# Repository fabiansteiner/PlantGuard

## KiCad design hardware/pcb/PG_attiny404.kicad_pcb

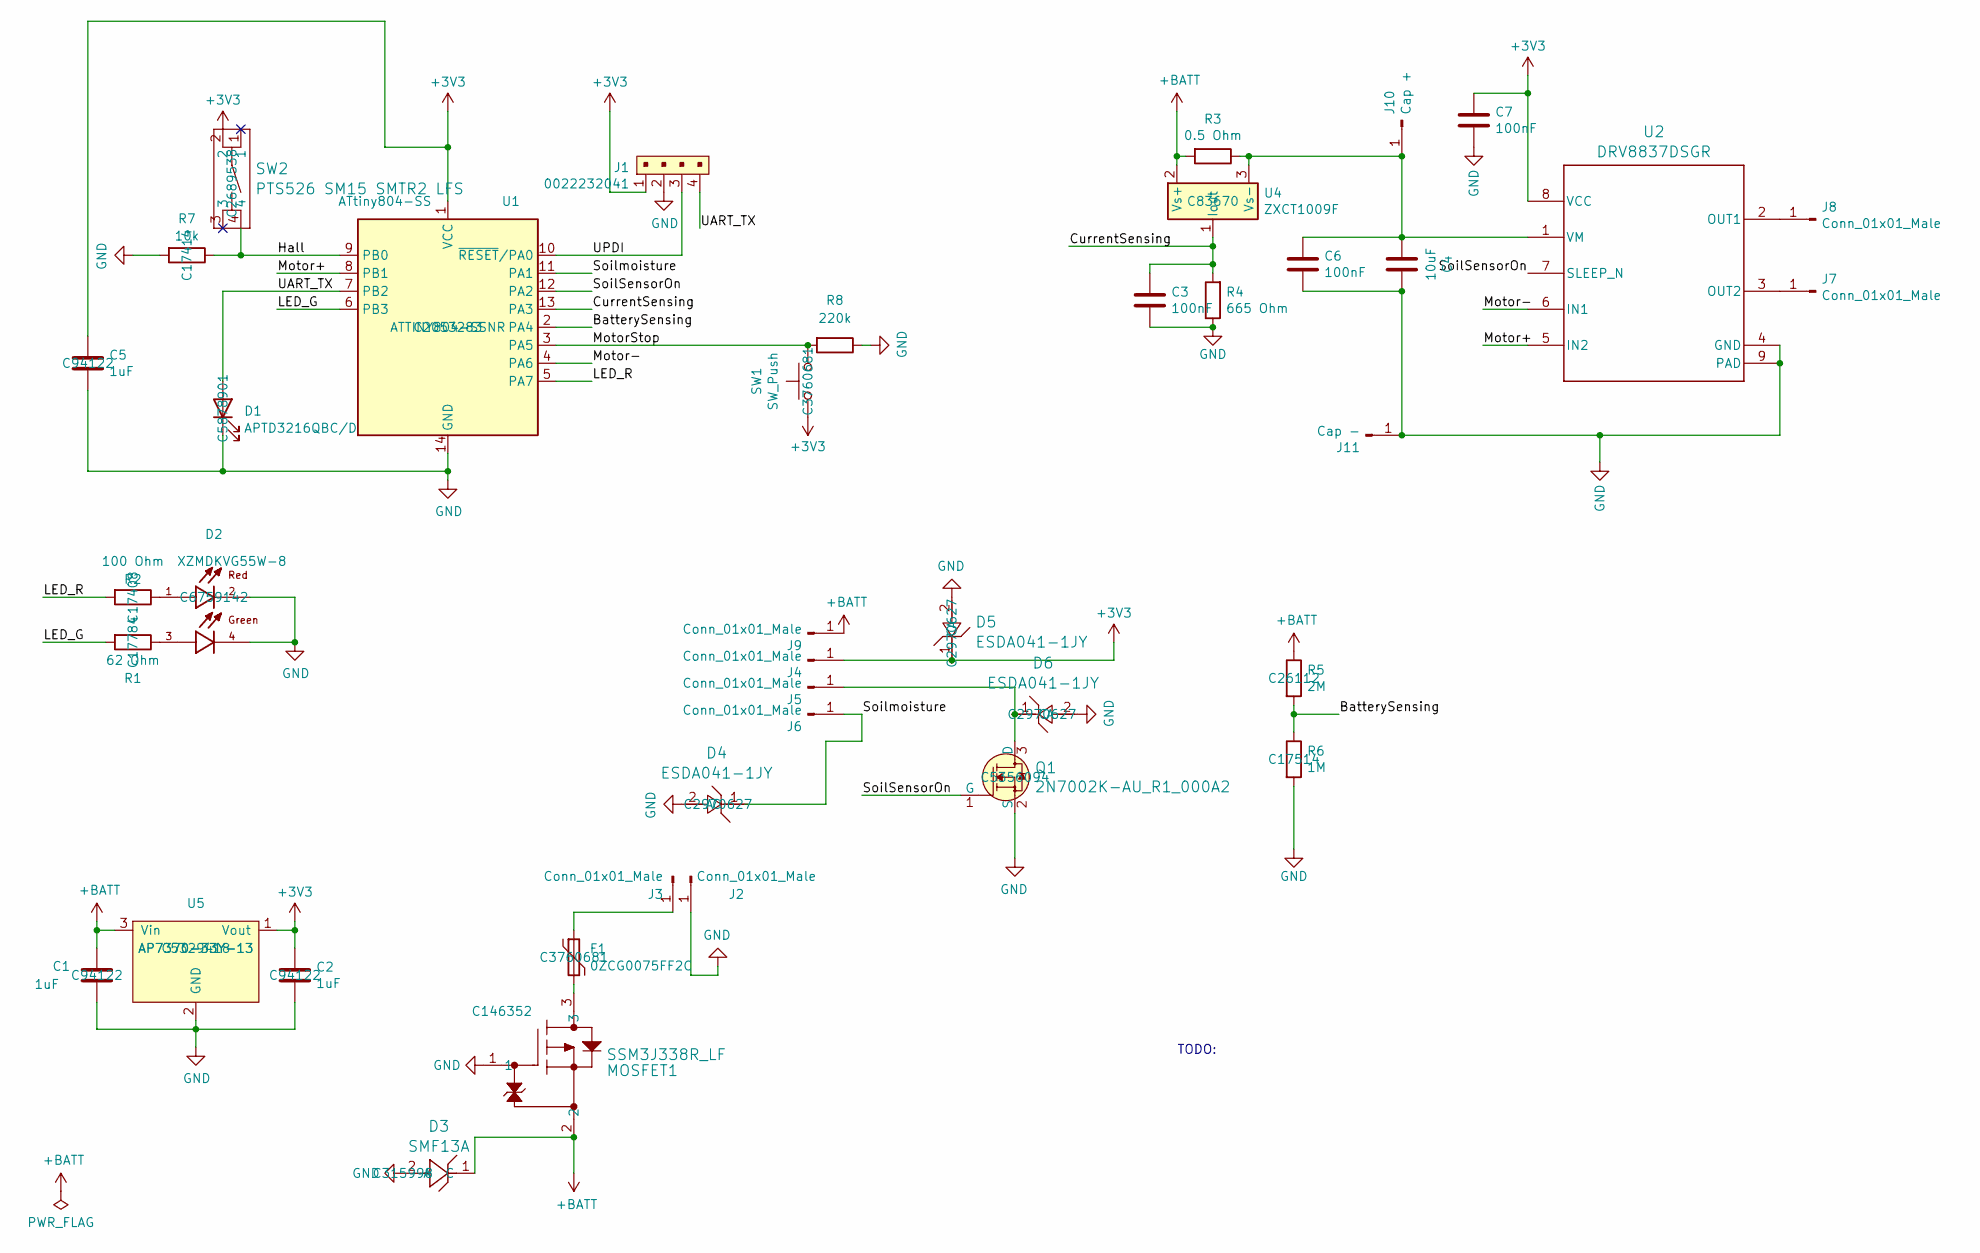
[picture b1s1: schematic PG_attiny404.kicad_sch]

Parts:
C1, C2, C5: 1uF; C_0805_2012Metric_Pad1.18x1.45mm_HandSolder; MPN CL21B105KOFNNNE; JLC C94122
C3, C6, C7: 100nF; C_0805_2012Metric_Pad1.18x1.45mm_HandSolder; MPN CC0805KRX7R7BB104; JLC C519980
C4: 10uF; C_0805_2012Metric_Pad1.18x1.45mm_HandSolder; MPN CL21A106KOQNNNG; JLC C326595
D1: APTD3216QBC/D; LED_1206_3216Metric_Pad1.42x1.75mm_HandSolder; MPN APTD3216QBC/D; JLC C5878901
D2: XZMDKVG55W-8; LED_XZMDKVG55W-8; MPN XZMDKVG55W-8; DigiKey_Part_Number 1497-1183-2-ND
D3: SMF13A; SMFSeries_LTF; MPN SMF13A; JLC C315998
D4, D5, D6: ESDA041-1JY; CR_041-1JY_STM; MPN ESDA041-1JY; JLC C2970627
F1: 0ZCG0075FF2C; MPN 0ZCG0075FF2C; JLC C3760681
J1: 0022232041; PinHeader_1x4_P2.54mm_Drill1.02mm; MPN 0022286040; Digi-Key_PN WM4202-ND
J2, J3, J4, J5, J6, J7, J8, J9: Conn_01x01_Male; PROBE_PAD_1206
J10: Cap +; PROBE_PAD_0603
J11: Cap -; PROBE_PAD_0603
MOSFET1: SSM3J338R_LF; SOT-23F_TOS; MPN SSM3J338R,LF; JLC C146352
Q1: 2N7002K-AU_R1_000A2; SOT-23_Handsoldering; MPN 2N7002K-AU_R1_000A2; Digi-Key_PN 2N7002NCT-ND
R1: 62 Ohm; R_0805_2012Metric_Pad1.20x1.40mm_HandSolder; MPN RMCF0805FT62R0; JLC C17784
R2: 100 Ohm; R_0805_2012Metric_Pad1.20x1.40mm_HandSolder; MPN RMCF0805FT100R; JLC C17408
R3: 0.5 Ohm; R_0805_2012Metric_Pad1.20x1.40mm_HandSolder; MPN RL1220S-R50-F; JLC C859814
R4: 665 Ohm; R_0805_2012Metric_Pad1.20x1.40mm_HandSolder; MPN CRGCQ0805F680R; JLC C17798
R5: 2M; R_0805_2012Metric_Pad1.20x1.40mm_HandSolder; MPN RMCF0805FT2M00; JLC C26112
R6: 1M; R_0805_2012Metric_Pad1.20x1.40mm_HandSolder; MPN RMCF0805FG1M00; JLC C17514
R7: 10k; R_0805_2012Metric_Pad1.20x1.40mm_HandSolder; MPN ERJ-6GEYJ103V; JLC C17414
R8: 220k; R_0805_2012Metric_Pad1.20x1.40mm_HandSolder; MPN CRG0805F220K; JLC C17556
SW1: SW_Push; 1825027-2; MPN 1825027-2; JLC C3760681
SW2: PTS526 SM15 SMTR2 LFS; PTS526SK15SMTR2 LFS-M; MPN PTS526SM15SMTR2 LFS; JLC C2689538
U1: ATtiny804-SS; SOIC-14_3.9x8.7mm_P1.27mm; MPN ATTINY804-SSNR; JLC C2053283
U2: DRV8837DSGR; DRV8837DSGR_NV; MPN DRV8837DSGR; JLC C39159
U4: ZXCT1009F; SOT-23_Handsoldering_ZXCT1009F; MPN ZXCT1009FTA; JLC C83670
U5: AP7370-33Y-13; SOT-89-3; MPN AP7370-33Y-13; JLC C5329418

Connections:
+3V3: C2.2, C5.2, C7.2, D5.1 (C), J1.1, J4.1, SW1.2, SW2.2, U1.1 (VCC), U2.8 (VCC), U5.1 (Vout)
+BATT: C1.2, D3.1 (C), J9.1, MOSFET1.2, R3.2, R5.1, U4.2 (Vs+), U5.3 (Vin)
/BatterySensing: R5.2, R6.1, U1.2 (PA4)
/CurrentSensing: C3.2, R4.2, U1.13 (PA3), U4.1 (Iout)
/Hall: R7.1, SW2.4, U1.9 (PB0)
/LED_G: R1.2, U1.6 (PB3)
/LED_R: R2.2, U1.5 (PA7)
/Motor+: U1.8 (PB1), U2.5 (IN2)
/Motor-: U1.4 (PA6), U2.6 (IN1)
/MotorStop: R8.2, SW1.1, U1.3 (PA5)
/SoilSensorOn: Q1.1 (G), U1.12 (PA2), U2.7 (SLEEP_N)
/Soilmoisture: D4.1 (C), J6.1, U1.11 (PA1)
/UART_TX: D1.2 (A), J1.4, U1.7 (PB2)
/UPDI: J1.3, U1.10 (~RESET/PA0)
GND: C1.1, C2.1, C3.1, C4.1, C5.1, C6.1, C7.1, D1.1 (K), D2.2, D2.4, D3.2 (A), D4.2 (A), D5.2 (A), D6.2 (A), J1.2, J2.1, J11.1, MOSFET1.1, Q1.2 (S), R4.1, R6.2, R7.2, R8.1, U1.14 (GND), U2.4 (GND), U2.9 (PAD), U5.2 (GND)
unnamed: D2.1, R2.1
unnamed: D2.3, R1.1
unnamed: D6.1 (C), J5.1, Q1.3 (D)
unnamed: F1.2, MOSFET1.3
unnamed: F1.1, J3.1
unnamed: J7.1, U2.3 (OUT2)
unnamed: J8.1, U2.2 (OUT1)
unnamed: C4.2, C6.2, J10.1, R3.1, U2.1 (VM), U4.3 (Vs-)

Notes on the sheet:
TODO:

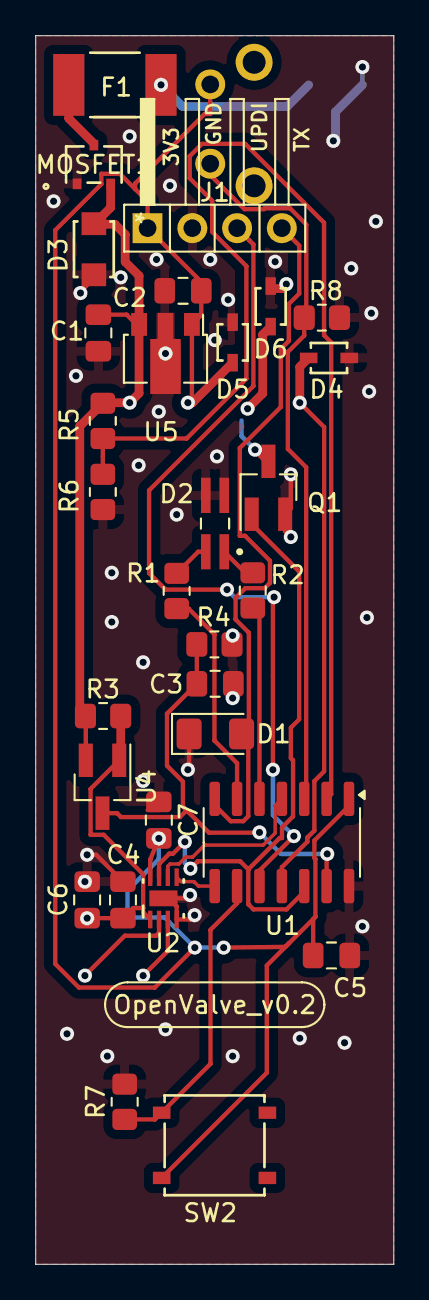
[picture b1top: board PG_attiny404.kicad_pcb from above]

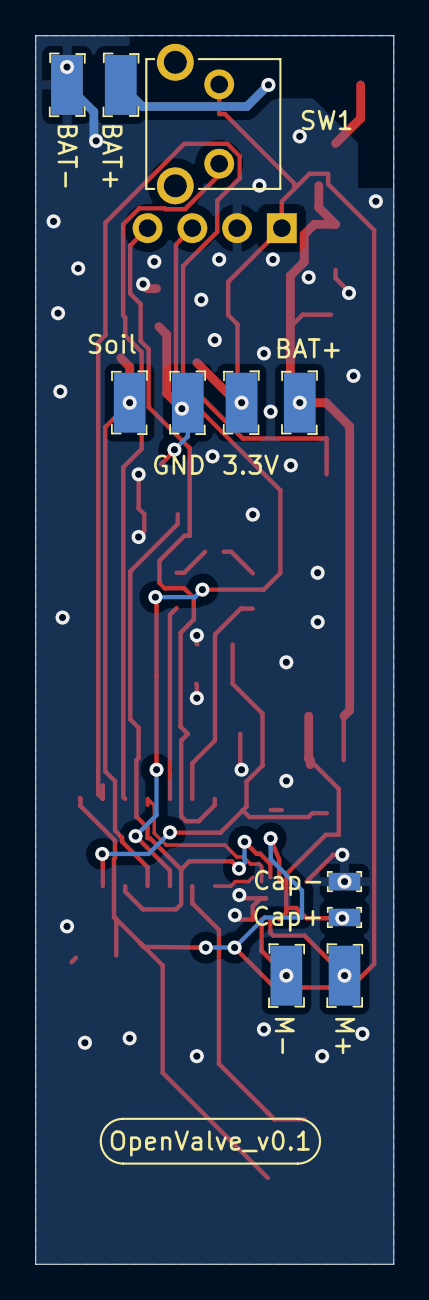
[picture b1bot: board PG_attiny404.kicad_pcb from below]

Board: 2 copper layers, 20.3 x 69.7 mm, 41 parts (11 on the bottom side), 23 nets.

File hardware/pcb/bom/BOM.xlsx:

Reference | Value | DK_Detail_Page | Menge
C1, C2, C5 | 1uF | https://www.digikey.at/de/products/detail/samsung-electro-me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 | 3
C3, C6 | 100nF | https://www.digikey.at/de/products/detail/yageo/CC0805KRX7R7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 | 2
C4 | 10uF | https://www.digikey.at/de/products/detail/samsung-electro-me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 | 1
D1 | APTD3216QBC/D | https://www.digikey.at/de/products/detail/kingbright/APTD321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 | 1
D2 | XZMDKVG55W-8 | https://www.digikey.at/de/products/detail/sunled/XZMDKVG55W-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 | 1
J1 | 0022232041 | https://www.digikey.at/de/products/detail/molex/0022286040/3158671 | 1
J2-J9 | Conn_01x01_Male |  | 8
Q1 | 2N7002 | https://www.digikey.at/de/products/detail/panjit-internation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 | 1
R1, R2 | 68 Ohm | https://www.digikey.at/de/products/detail/stackpole-electron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 | 2
R3 | 0.5 Ohm | https://www.digikey.at/de/products/detail/susumu/RL1220S-R50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 | 1
R4 | 665 Ohm | https://www.digikey.at/de/products/detail/te-connectivity-pa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 | 1
R5 | 2M | https://www.digikey.at/de/products/detail/stackpole-electron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 | 1
R6 | 1M | https://www.digikey.at/de/products/detail/stackpole-electron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 | 1
SW1 | SW_Push | https://www.digikey.at/de/products/detail/te-connectivity-al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 | 1
U1 | ATtiny404-SS | https://www.digikey.at/de/products/detail/microchip-technolo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 | 1
U2 | AH9246 | https://www.digikey.at/de/products/detail/diodes-incorporate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 | 1
U4 | ZXCT1009F | https://www.digikey.at/de/products/detail/diodes-incorporate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 | 1
U5 | AP7370-33Y-13 | https://www.digikey.at/de/products/detail/diodes-incorporate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 | 1
U6 | MP6513GJ | https://www.digikey.at/de/products/detail/monolithic-power-s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 | 1

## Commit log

2022-10-16 Added working Microchip Studio Project with blinky + UART output
2022-11-12 Added necessary interfaces
2022-12-01 Added Functionality: Valve open, Valve close; Added functionality: Read Soil Moisture Sensor
2023-01-06 Basic functionality established: Valve opens when ADC Reading from soil moisture sensor above 512 and closes when its below
2023-01-22 Make LED glow when Magnet sensor is on
2023-02-17 Small modifications of values in valve opening/closing, Added Interfaces for UI
2023-02-17 Actual merge (fail)
2023-02-19 Added LED animations
2023-02-26 Added User Interface and Battery Sensing
2023-03-09 Added Sleep functionality
2023-05-21 Fixed bug: Program got stuck in while loop when ADC was occupied and never released, other small improvements
2023-09-09 Added pcb
2023-10-14 Equiped PCB with additional led, changed other led, changed position of solder pads and side of hall sensor
2023-10-25 Added Interactive Bom
2023-10-27 Restructured Software, Added Support for Blue LED
2023-10-27 Updated gitignores
2024-02-11 Significantly improved valve control code to detect drained battery and other possible errors like broken hardware
2024-02-26 Added manual irrigation, Added a different animation for timeout than confirmation
2024-02-26 Added turning valve on and off, added software version animation, improved other animations
2024-03-03 Error States (different fail saves) are displayed now - User can look up which error occured
2024-03-11 Added Multiplicator Setting with variable sleep time; Added timeout for manual irrigation mode
2024-03-16 Added Reverse voltage protection on PCB
2024-03-18 Changed some parameters regarding valve opening/closing
2024-06-17 Motor code polishing, Added p-channel to pcb for reverse voltage protection
2024-06-23 Corrections
2024-06-30 Fixed bug: Freeze at startup, small UI corrections: Faster recognition of long button presses, Corrected Version, instead of blink steady glow when slecting settings
2024-07-30 Added Correct Sensor interpretation for SoilWatch 10
2024-08-02 Fixed wrong ADC voltage reference for soil moisture sensor, started logic for supporting different soild moisture sensors, standby led now blinks in standby mode when valve is open instead of glowing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
2025-01-21 Changed closing/opening logic for faster curr measurment rate
2025-04-08 New PCB Version 0.1
2025-04-11 Footprint correction for Current Sensor
2025-04-19 Added new motor driver to pcb
2025-04-19 Changed Software to work with new Pull down Resistors and new Motor driver
2025-05-21 Motor PWM Rampup for lower voltage drop; Valve doesnt open if battery is below 7V; Multiple Closing attempts before entering HIGH CURRENT error; Introduced new valveState: WRONG_SENSOR_PLACEMENT -> a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
2025-05-25 Made blink count animations slightly slower; Fixed bug where showing current soil moisture animation was behaving wrong because the value got updated mid animation
2025-05-30 Small Changes for Ordering PCB
2025-07-27 Improved valve opening logic

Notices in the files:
parts and their libraries:
Copyright 2021 Accelerated Designs. All rights reserved.
